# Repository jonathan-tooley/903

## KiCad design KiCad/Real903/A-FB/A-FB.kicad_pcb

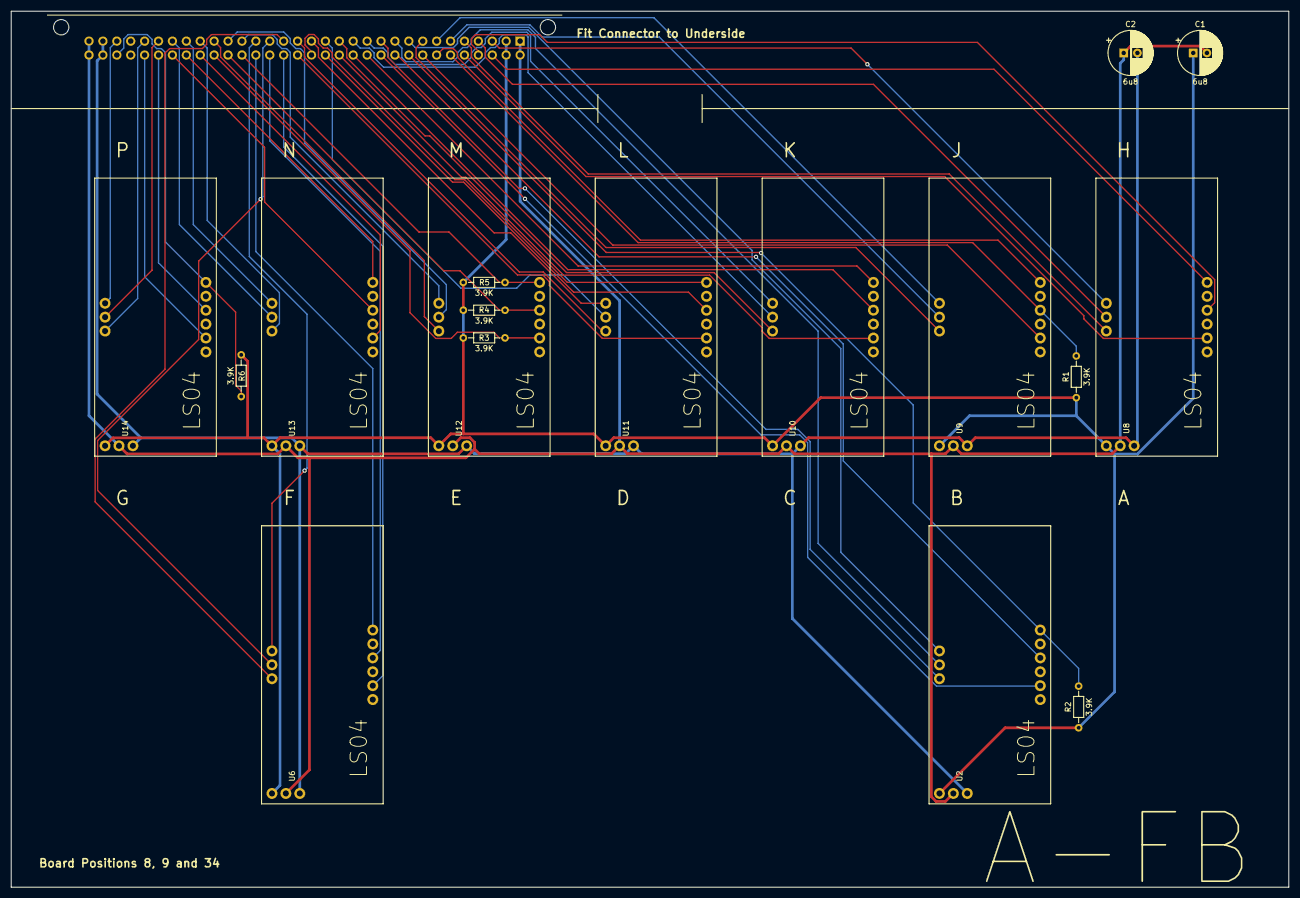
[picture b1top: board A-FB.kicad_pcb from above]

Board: 2 copper layers, 233.3 x 160.0 mm, 18 parts (1 on the bottom side), 57 nets.

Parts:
C1, C2: 6u8; CP_Radial_D8.0mm_P2.50mm
J1: J1; DIN41612_B_2x32_Horizontal
R1, R2, R3, R4, R5, R6: 3.9K; R_Axial_DIN0204_L3.6mm_D1.6mm_P7.62mm_Horizontal
U2, U6, U8, U9, U10, U11, U12, U13, U14: LS04; LSA

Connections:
3: J1.3, U8.13
4: J1.4, U8.12
5: J1.5, U8.11
6: J1.6, U9.12
6v: C1.1, J1.2, J1.B, R1.1, R2.1, R3.1, R4.1, R5.1, R6.1, U2.21, U6.21, U8.21, U9.21, U10.21, U11.21, U12.21, U13.21, U14.21
7: J1.7, U9.13
8: J1.8, U9.11
9: J1.9, U2.13
10: J1.10, U2.12
11: J1.11, U2.11
12: J1.12, U10.13
13: J1.13, U10.12
14: J1.14, U10.11
15: J1.15, U11.12
16: J1.16, U11.13
17: J1.17, U11.11
18: J1.18, U6.11
19: J1.19, U6.12
20: J1.20, U6.13
21: J1.21, U12.13
22: J1.22, U12.12
23: J1.23, U12.11
24: J1.24, U13.11
25: J1.25, U13.13
26: J1.26, U13.12
27: J1.27, U14.12
28: J1.28, U14.11
30: J1.30, U14.13
AA: J1.AA, R3.2, U12.2
AB: J1.AB, U13.2
AC: J1.AC, U13.6
AD: J1.AD, U13.4
AE: J1.AE, U14.4
AF: J1.AF, U14.2
AJ: J1.AJ, R6.2, U14.6
C: J1.C, U8.6
D: J1.D, U8.4
E: J1.E, U8.2
F: J1.F, R1.2, U9.4
GND: C1.2, C2.1, J1.1, J1.32, J1.A, J1.AL, U2.22, U6.22, U8.22, U9.22, U10.22, U11.22, U12.22, U13.22, U14.22
H: J1.H, U9.6
J: J1.J, U9.2
K: J1.K, R2.2, U2.6
L: J1.L, U2.4
M: J1.M, U2.2
N: J1.N, U10.6
Neg6v: C2.2, J1.31, J1.AK, U2.23, U6.23, U8.23, U9.23, U10.23, U11.23, U12.23, U13.23, U14.23
P: J1.P, U10.4
R: J1.R, U10.2
S: J1.S, U11.4
T: J1.T, U11.6
U: J1.U, U11.2
V: J1.V, U6.2
W: J1.W, U6.4
X: J1.X, U6.6
Y: J1.Y, R5.2, U12.6
Z: J1.Z, R4.2, U12.4

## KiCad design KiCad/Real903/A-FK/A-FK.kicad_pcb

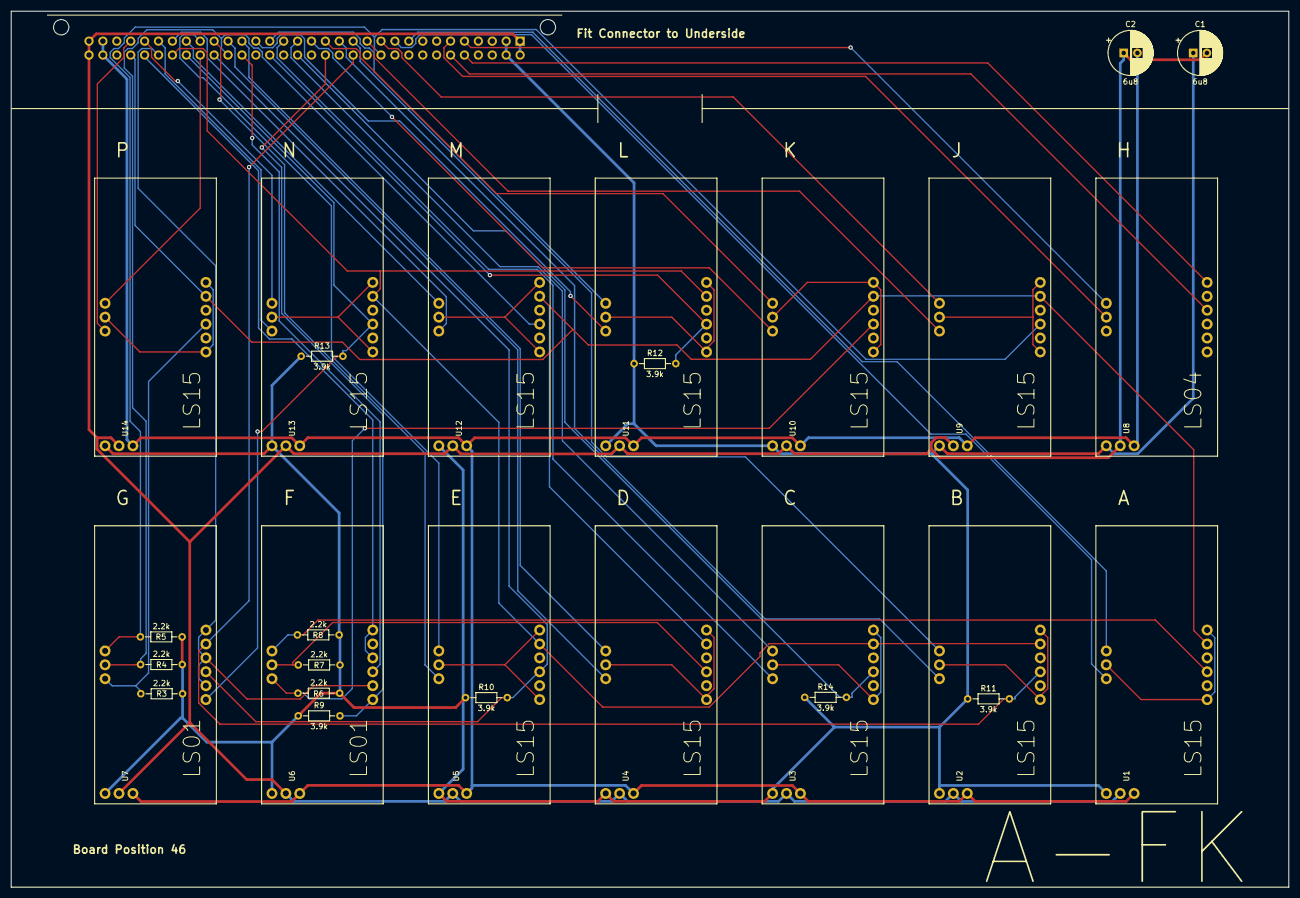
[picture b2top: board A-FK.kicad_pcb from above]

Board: 2 copper layers, 233.3 x 160.0 mm, 29 parts (1 on the bottom side), 57 nets.

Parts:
C1, C2: 6u8; CP_Radial_D8.0mm_P2.50mm
J1: J1; DIN41612_B_2x32_Horizontal
R3, R4, R5, R6, R7, R8: 2.2k; R_Axial_DIN0204_L3.6mm_D1.6mm_P7.62mm_Horizontal
R9, R10, R11, R12, R13, R14: 3.9k; R_Axial_DIN0204_L3.6mm_D1.6mm_P7.62mm_Horizontal
U1, U2, U3, U4, U5, U9, U10, U11, U12, U13, U14: LS15; LSA
U6, U7: LS01; LSA
U8: LS04; LSA

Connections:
6v: C1.1, J1.2, J1.B, R3.1, R4.1, R5.1, R6.1, R7.1, R8.1, R9.1, R10.1, R11.1, R12.1, R13.1, R14.1, U1.21, U2.21, U3.21, U4.21, U5.21, U6.21, U7.21, U8.21, U9.21, U10.21, U11.21, U12.21, U13.21, U14.21
CRS: J1.5, U8.13
CRSm: J1.E, U8.6
GND: C1.2, C2.1, J1.1, J1.32, J1.A, J1.AL, U1.22, U2.22, U3.22, U4.22, U5.22, U6.22, U7.22, U8.22, U9.22, U10.22, U11.22, U12.22, U13.22, U14.22
GTA1: J1.23, U5.11
GTA2: J1.24, U5.13
GTAa: J1.AA, R10.2, U5.3, U7.3
GTJ1: J1.13, U2.13
GTJ2: J1.14, U2.11
GTJa: J1.P, R11.2, U2.3, U7.5
GTM1: J1.19, U11.13
GTM2: J1.20, U11.11
GTMa: J1.W, R12.2, U11.3
GTQ1: J1.27, U13.11
GTQ2: J1.28, U13.13
GTQa: J1.AC, R13.2, U7.1, U13.3
MTPa: J1.Y, U6.3
Neg6v: C2.2, J1.31, J1.AK, U1.23, U2.23, U3.23, U4.23, U5.23, U6.23, U7.23, U8.23, U9.23, U10.23, U11.23, U12.23, U13.23, U14.23
unnamed: R3.2, U7.11, U14.3
unnamed: R6.2, U6.11, U10.3
unnamed: R7.2, U4.3, U6.12
unnamed: R8.2, U1.3, U6.13
unnamed: U1.1, U1.6, U1.12
unnamed: U2.1, U2.6, U2.12
unnamed: U3.1, U3.6, U3.12
unnamed: U4.1, U4.6, U4.12
unnamed: U5.1, U5.6, U5.12
unnamed: U9.1, U9.6, U9.12
unnamed: U10.1, U10.6, U10.12
unnamed: U11.1, U11.6, U11.12
unnamed: U12.1, U12.6, U12.12
unnamed: U13.1, U13.6, U13.12
unnamed: U14.1, U14.6, U14.12
OTA-1: J1.25, U12.13
OTA-2: J1.26, U12.11
OTA-': J1.Z, R4.2, U7.12, U12.3
OTG-1: J1.9, U1.13
OTG-2: J1.10, U1.11
OTJ-1: J1.11, U9.13
OTJ-2: J1.12, U9.11
OTJ-': J1.M, R5.2, U7.13, U9.3
OTM-1: J1.15, U10.13
OTM-2: J1.16, U10.11
OTMa: J1.S, R9.2, U6.1
OTP-1: J1.21, U4.13
OTP-2: J1.22, U4.11
OTQ-1: J1.29, U14.11
OTQ-2: J1.AB, U14.13
RESET-2: J1.AH, U1.5, U4.5, U9.5, U10.5, U12.5, U14.5
SFD: J1.6, U8.12
SFDm: J1.F, U8.4
WTM1: J1.17, U3.13
WTM2: J1.18, U3.11
WTMa: J1.U, R14.2, U3.3
t1: J1.AF, U6.4, U6.6
t3-2: J1.AE, U6.2, U7.2, U7.4, U7.6
t4: J1.AD, U2.5, U3.5, U5.5, U11.5, U13.5

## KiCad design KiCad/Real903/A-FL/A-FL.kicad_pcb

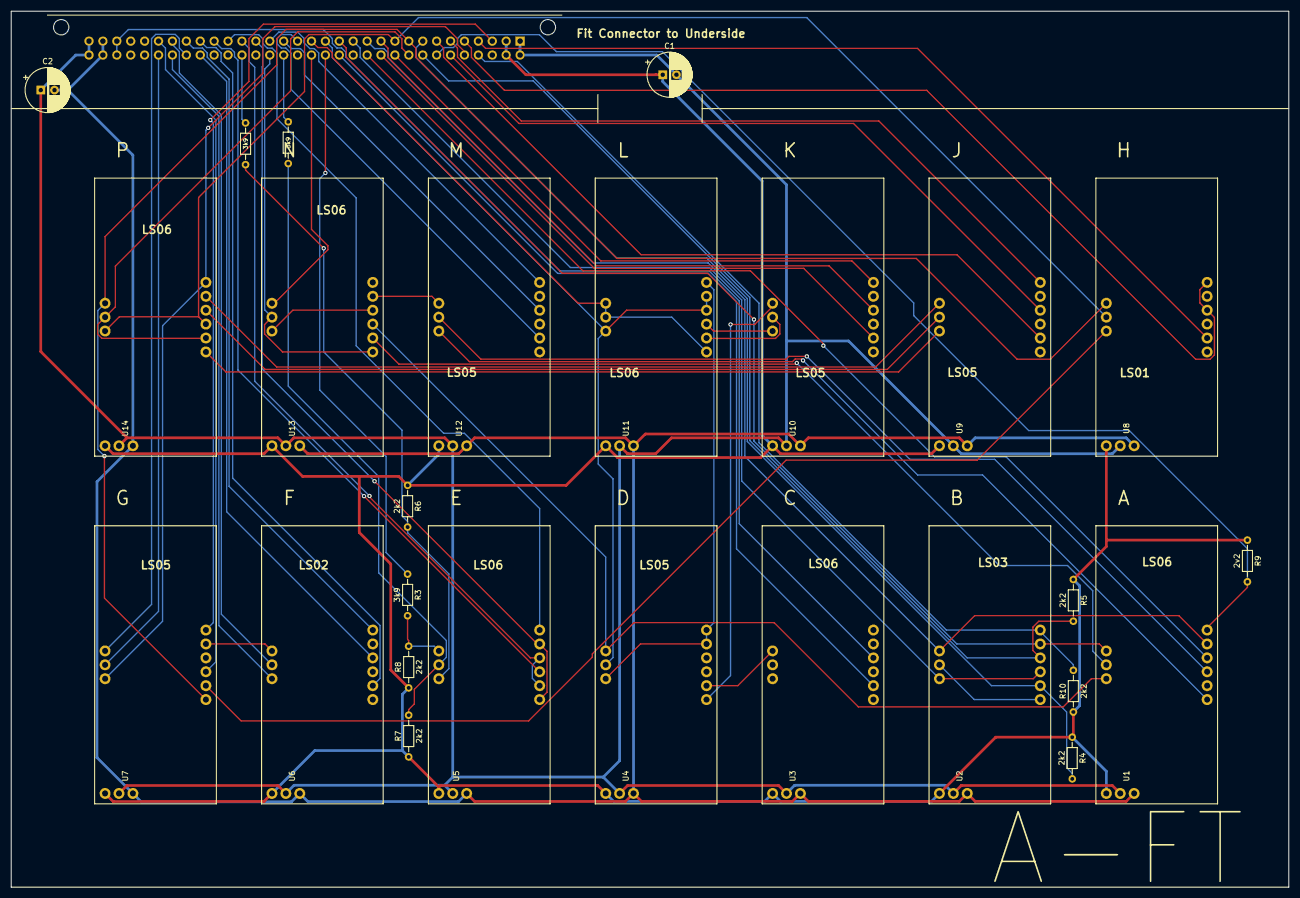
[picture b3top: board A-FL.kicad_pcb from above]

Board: 2 copper layers, 233.3 x 160.0 mm, 27 parts (1 on the bottom side), 68 nets.

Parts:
C1, C2: "6u8"; CP_Radial_D8.0mm_P2.50mm
J1: J1; DIN41612_B_2x32_Horizontal
R1, R2, R3: 3k9; R_Axial_DIN0204_L3.6mm_D1.6mm_P7.62mm_Horizontal
R4, R5, R6, R7, R8, R10: 2k2; R_Axial_DIN0204_L3.6mm_D1.6mm_P7.62mm_Horizontal
R9: 2v2; R_Axial_DIN0204_L3.6mm_D1.6mm_P7.62mm_Horizontal
U1, U2, U5, U7, U11, U13, U14: LS01; LSA
U3: LS14; LSA
U4: LS03; LSA
U6, U8, U9, U10, U12: LS18; LSA

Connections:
2.4v: J1.30, J1.AJ, U3.4
6v: C1.1, J1.2, J1.B, R4.1, R5.1, R6.1, R7.1, R8.1, R9.1, R10.1, U1.21, U2.21, U3.21, U4.21, U5.21, U6.21, U7.21, U8.21, U9.21, U10.21, U11.21, U12.21, U13.21, U14.21
AUTOk: J1.L, U10.6
CIN: J1.13, U2.3, U2.11
CINSk: J1.J, R5.2, U2.4
CS: J1.14, U1.13, U2.5
E1: J1.23, U5.3
E2: J1.22, U5.6
ENG: J1.9, U7.1, U8.13, U14.13
ENGk: J1.6, U9.6
GND: C1.2, C2.1, J1.1, J1.32, J1.A, J1.AL, U1.22, U2.22, U3.22, U4.22, U5.22, U6.22, U7.22, U8.22, U9.22, U10.22, U11.22, U12.22, U13.22, U14.22
JUMP: J1.16, U11.1, U11.12, U11.13
JUMPk: J1.M, U10.2
NG17k: J1.18, U12.4
Neg6v: C2.2, J1.31, J1.AK, U1.23, U2.23, U3.23, U4.23, U5.23, U6.23, U7.23, U8.23, U9.23, U10.23, U11.23, U12.23, U13.23, U14.23
unnamed: R1.2, R6.2, U5.11
unnamed: R2.2, R7.2, U5.12
unnamed: R3.2, R8.2, U5.13
unnamed: U1.1, U12.11
unnamed: U1.3, U12.12
unnamed: U1.11, U4.13, U13.3
unnamed: U1.12, U13.2
unnamed: U2.1, U2.12
unnamed: U3.13, U4.2
unnamed: U6.13, U7.5
unnamed: U7.2, U8.11
unnamed: U10.11, U11.3
unnamed: U10.12, U11.2
unnamed: U4.1, U10.13
unnamed: U4.5, U4.6, U4.11, U11.6
unnamed: U12.13, U13.5
unnamed: U13.4, U13.11
unnamed: U9.11, U14.1
unnamed: U9.12, U14.4
unnamed: U9.13, U14.5
ONG: J1.10, U8.12, U14.3, U14.11
ONGk: J1.7, U9.2
RESET: J1.AE, U7.12
RESETk: J1.24, U6.2
TCS: J1.26, U6.12
W17: J1.W, U13.1, U13.12
{ACTIVE1}: J1.Y, R1.1
{ACTIVE2}: J1.V, R2.1
{ACTIVE3}: J1.S, R3.1
~CINSk~: J1.8, R4.2, U2.2
~CSk~: J1.H, R9.2, U1.6
~CS~: J1.12, U1.5, U2.13
~E1~: J1.20, U5.1, U5.5
~E2~: J1.21, U5.2, U5.4
~ENGk~: J1.4, U8.2
~ENG~: J1.E, U7.11, U14.6
~JIA~: J1.R, U3.2
~JUMP~: J1.15, U4.12, U11.4, U11.5, U11.11
~JUMP~k: J1.11, U10.4
~NG17~k: J1.17, U12.2
~ONGk~: J1.F, U9.4
~ONG~: J1.K, U14.2, U14.12
~OS~: J1.T, U13.13
~OS~k: J1.19, U12.6
~RESET~: J1.AD, U6.11
~RESET~1: J1.27, U7.3
~RESTART~K: J1.3, U7.6
~SMNk~: J1.D, R10.2, U2.6
~STOP~: J1.AC, U7.13
~STOP~k: J1.25, U6.6
~TCS~k: J1.AB, U6.4
~TEST~k: J1.5, U8.4, U8.6
~WTM~a: J1.N, U1.4

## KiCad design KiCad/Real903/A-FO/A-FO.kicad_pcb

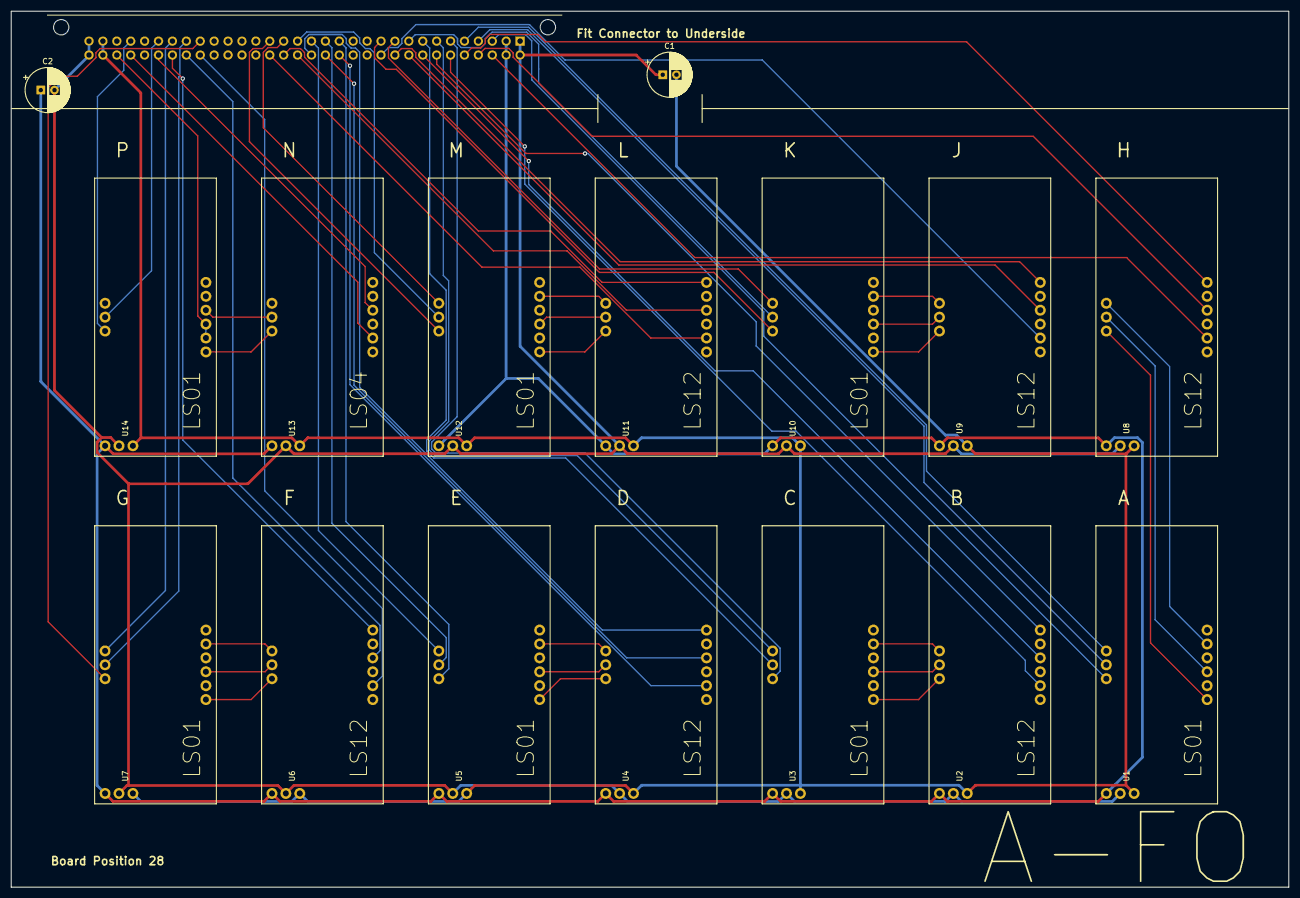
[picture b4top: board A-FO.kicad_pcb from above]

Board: 2 copper layers, 233.3 x 160.0 mm, 17 parts (1 on the bottom side), 64 nets.

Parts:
C1, C2: 6u8; CP_Radial_D8.0mm_P2.50mm
J1: J1; DIN41612_B_2x32_Horizontal
U1, U3, U5, U7, U10, U12, U14: LS01; LSA
U2, U4, U6, U8, U9, U11: LS12; LSA
U13: LS04; LSA

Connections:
6v: C2.1, J1.2, J1.B, U1.21, U2.21, U3.21, U4.21, U5.21, U6.21, U7.21, U8.21, U9.21, U10.21, U11.21, U12.21, U13.21, U14.21
GND: C1.1, C2.2, J1.1, J1.32, J1.A, J1.AL, U1.22, U2.22, U3.22, U4.22, U5.22, U6.22, U7.22, U8.22, U9.22, U10.22, U11.22, U12.22, U13.22, U14.22
IG1: J1.C, U8.2
IG2: J1.D, U8.4
IG3: J1.E, U8.6
IG4: J1.F, U2.2
IG5: J1.H, U2.6
IG6: J1.J, U2.4
IG7: J1.K, U9.4
IG8: J1.L, U9.6
IG9: J1.M, U9.2
IG10: J1.R, U4.2
IG11: J1.S, U4.4
IG12: J1.T, U4.6
IG13: J1.U, U11.4
IG14: J1.V, U11.6
IG15: J1.W, U11.2
IG16: J1.AB, U6.2
IG17: J1.AC, U6.4
IG18: J1.AD, U6.6
IP1: J1.3, U1.11
IP2: J1.4, U1.12
IP3: J1.5, U1.13
IP4: J1.6, U3.11
IP5: J1.7, U3.13
IP6: J1.8, U3.12
IP7: J1.9, U10.12
IP8: J1.10, U10.13
IP9: J1.11, U10.11
IP10: J1.14, U5.11
IP11: J1.15, U5.12
IP12: J1.16, U5.13
IP13: J1.17, U12.12
IP14: J1.18, U12.13
IP15: J1.19, U12.11
IP16: J1.24, U7.11
IP17: J1.25, U7.12
IP18: J1.26, U7.13
Neg6v: C1.2, J1.31, J1.AK, U1.23, U2.23, U3.23, U4.23, U5.23, U6.23, U7.23, U8.23, U9.23, U10.23, U11.23, U12.23, U13.23, U14.23
unnamed: U1.1, U8.11
unnamed: U1.3, U8.12
unnamed: U1.5, U8.13
unnamed: U2.11, U3.1
unnamed: U2.12, U3.3
unnamed: U2.13, U3.5
unnamed: U4.11, U5.1
unnamed: U4.12, U5.3
unnamed: U4.13, U5.5
unnamed: U6.11, U7.1
unnamed: U6.12, U7.3
unnamed: U6.13, U7.5
unnamed: U9.11, U10.1
unnamed: U9.12, U10.3
unnamed: U9.13, U10.5
unnamed: U11.11, U12.1
unnamed: U11.12, U12.3
unnamed: U11.13, U12.5
unnamed: U13.11, U14.1
unnamed: U13.12, U14.4
RBT: J1.27, U14.12
RBTm: J1.AE, U13.4
SBT: J1.29, U14.11
SBTm: J1.AH, U13.2
t4-2: J1.AJ, U14.2, U14.3

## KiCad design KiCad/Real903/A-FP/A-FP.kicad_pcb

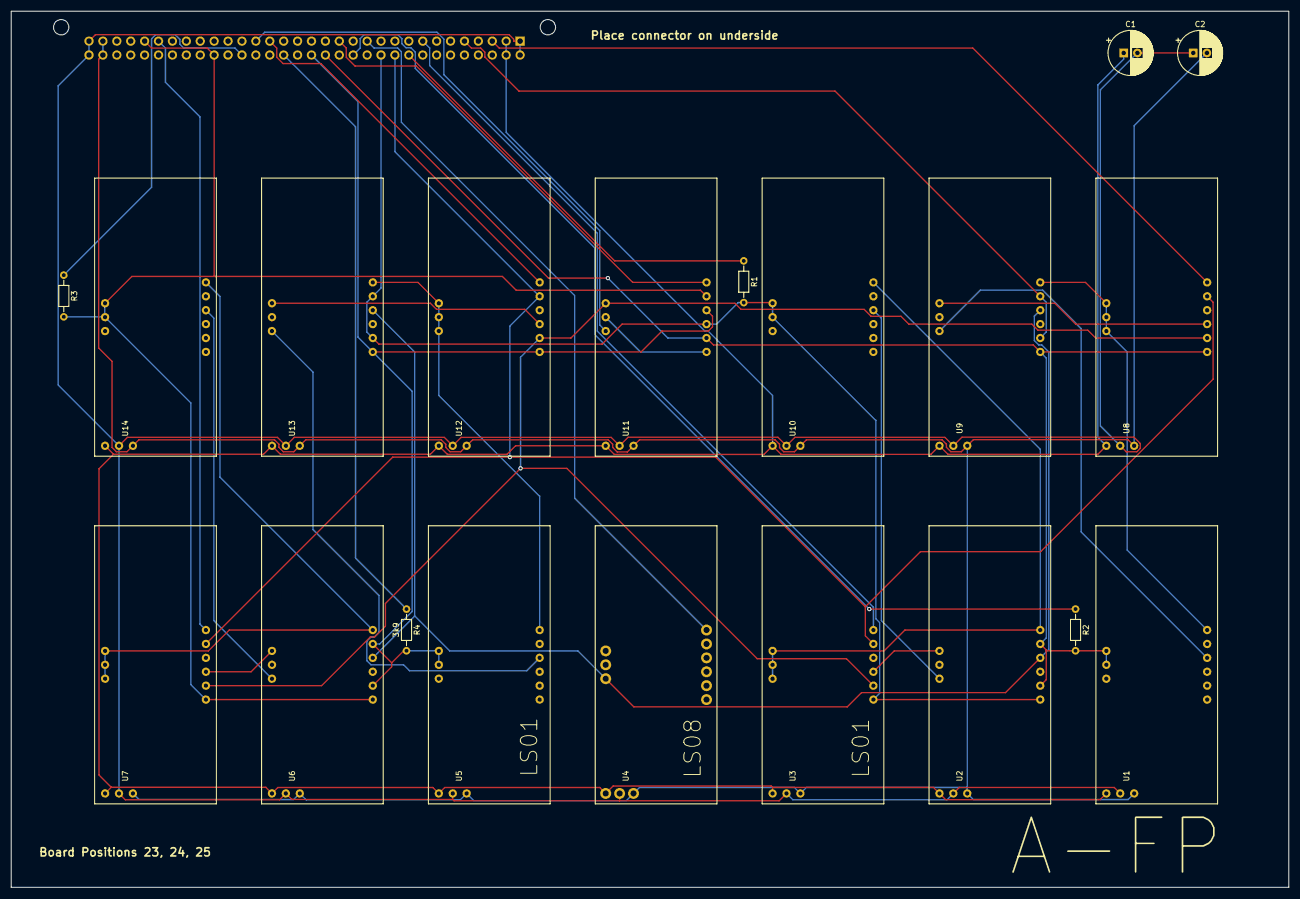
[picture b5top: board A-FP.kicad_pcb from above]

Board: 2 copper layers, 233.3 x 160.0 mm, 21 parts (1 on the bottom side), 35 nets.

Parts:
C1, C2: 6u8; CP_Radial_D8.0mm_P2.50mm
J1: J1; DIN41612_B_2x32_Horizontal
R1, R2, R3, R4: 3k9; R_Axial_DIN0204_L3.6mm_D1.6mm_P7.62mm_Horizontal
U1, U3, U5, U7, U8, U10, U12, U14: LS01; LSA
U2, U6, U9, U13: LS07; LSA
U4: LS08; LSA
U11: LS03; LSA

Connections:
1TPC-: J1.5, U9.2, U9.5
2.4vRef: U2.4, U4.11, U6.4, U9.4, U13.4
6v: C1.1, J1.2, J1.B, U1.21, U2.21, U3.21, U4.21, U5.21, U6.21, U7.21, U8.21, U9.21, U10.21, U11.21, U12.21, U13.21, U14.21
GND: C1.2, C2.1, J1.1, J1.32, J1.A, J1.AL, U1.22, U2.22, U3.22, U4.22, U5.22, U6.22, U7.22, U8.22, U9.22, U10.22, U11.22, U12.22, U13.22, U14.22
J1-: J1.3, U8.6
J2-: J1.8, U3.6
J3-: J1.19, U12.6
J4-: J1.27, U7.6
JTPC: J1.L, U3.5, U7.5, U8.5, U12.5
Neg6v: C2.2, J1.31, J1.AK, U1.23, U2.23, U3.23, U4.23, U5.23, U6.23, U7.23, U8.23, U9.23, U10.23, U11.23, U12.23, U13.23, U14.23
unnamed: U1.4, U9.11
unnamed: U1.6, U8.11, U8.12, U8.13, U9.6
unnamed: U2.13, U3.3
unnamed: U6.13, U7.3
unnamed: U8.3, U9.13
unnamed: U2.11, U10.4
unnamed: U2.6, U3.11, U3.12, U3.13, U10.6
unnamed: U11.1, U11.12
unnamed: U12.3, U13.13
unnamed: U5.6, U12.11, U12.12, U12.13, U13.6
unnamed: U5.4, U13.11
unnamed: U6.11, U14.4
unnamed: U6.6, U7.11, U7.12, U7.13, U14.6
PC1-: J1.S, R2.2, U1.12, U1.13, U2.2, U2.5, U8.1, U9.1, U11.2
PC1-4: J1.20, U11.11
PC2-: J1.M, R1.2, U2.1, U3.1, U10.12, U10.13, U11.3, U13.2, U13.5
PC3-: J1.T, R4.2, U5.12, U5.13, U6.2, U6.5, U11.4, U12.1, U13.1
PC4-: J1.28, J1.AA, R3.2, U6.1, U7.1, U11.5, U14.12, U14.13
PulseGenMargin: J1.12, U4.6
WFM-: U3.2, U7.2, U8.2, U11.13, U12.2
WFR: J1.14, U11.6
{PC1}: J1.P, R2.1
{PC2}: J1.K, R1.1
{PC3}: J1.V, R4.1
{PC4}: J1.Y, R3.1

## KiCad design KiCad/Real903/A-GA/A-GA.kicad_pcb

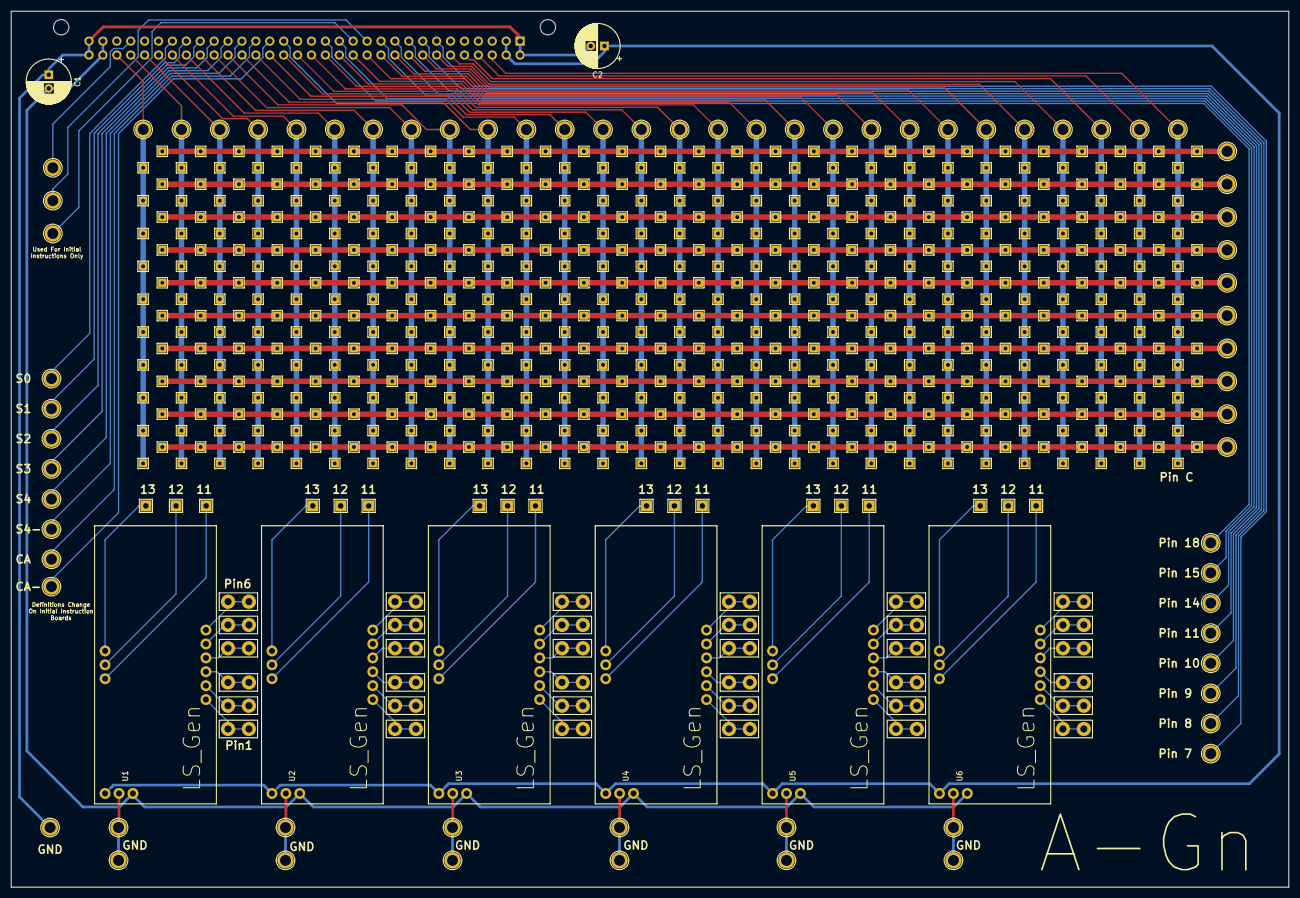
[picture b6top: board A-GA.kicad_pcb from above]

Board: 2 copper layers, 233.3 x 160.0 mm, 693 parts (1 on the bottom side), 120 nets.

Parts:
C1, C2: 6u8; CP_Radial_D8.0mm_P2.50mm
J1: J1; DIN41612_B_2x32_Horizontal
MH1, MH2, MH3, MH4, MH5, MH6, MH7, MH8, MH9, MH10, MH11, MH12, MH13, MH14, MH15, MH16, MH17, MH18, MH19, MH20, MH21, MH22, MH23, MH24, MH25, MH26, MH27, MH28, MH29, MH30, MH31, MH32, MH33, MH34, MH35, MH36, MH37, MH38, MH39, MH40, MH41, MH42, MH43, MH44, MH45, MH46, MH47, MH48, MH49, MH50, MH51, MH52, MH53, MH54, MH55, MH56, MH57, MH58, MH59, MH60, MH61, MH62, MH63, MH64, MH65, MH66, MH67, MH68, MH69, MH70, MH71, MH72, MH73, MH74, MH75, MH76, MH77, MH78, MH79, MH80, MH81, MH82, MH83, MH84, MH85, MH86, MH87, MH88, MH89, MH90, MH91, MH92, MH93, MH94, MH95, MH96, MH97, MH98, MH99, MH100, MH101, MH102, MH103, MH104, MH105, MH106, MH107, MH108, MH109, MH110, MH111, MH112, MH113, MH114, MH115, MH116, MH117, MH118, MH119, MH120, MH121, MH122, MH123, MH124, MH125, MH126, MH127, MH128, MH129, MH130, MH131, MH132, MH133, MH134, MH135, MH136, MH137, MH138, MH139, MH140, MH141, MH142, MH143, MH144, MH145, MH146, MH147, MH148, MH149, MH150, MH151, MH152, MH153, MH154, MH155, MH156, MH157, MH158, MH159, MH160, MH161, MH162, MH163, MH164, MH165, MH166, MH167, MH168, MH169, MH170, MH171, MH172, MH173, MH174, MH175, MH176, MH177, MH178, MH179, MH180, MH181, MH182, MH183, MH184, MH185, MH186, MH187, MH188, MH189, MH190, MH191, MH192, MH193, MH194, MH195, MH196, MH197, MH198, MH199, MH200, MH201, MH202, MH203, MH204, MH205, MH206, MH207, MH208, MH209, MH210, MH211, MH212, MH213, MH214, MH215, MH216, MH217, MH218, MH219, MH220, MH221, MH222, MH223, MH224, MH225, MH226, MH227, MH228, MH229, MH230, MH231, MH232, MH233, MH234, MH235, MH236, MH237, MH238, MH239, MH240, MH241, MH242, MH243, MH244, MH245, MH246, MH247, MH248, MH249, MH250, MH251, MH252, MH253, MH254, MH255, MH256, MH257, MH258, MH259, MH260, MH261, MH262, MH263, MH264, MH265, MH266, MH267, MH268, MH269, MH270, MH271, MH272, MH273, MH274, MH275, MH276, MH277, MH278, MH279, MH280, MH281, MH282, MH283, MH284, MH285, MH286, MH287, MH288, MH289, MH290, MH291, MH292, MH293, MH294, MH295, MH296, MH297, MH298, MH299, MH300, MH301, MH302, MH303, MH304, MH305, MH306, MH307, MH308, MH309, MH310, MH311, MH312, MH313, MH314, MH315, MH316, MH317, MH318, MH319, MH320, MH321, MH322, MH323, MH324, MH325, MH326, MH327, MH328, MH329, MH330, MH331, MH332, MH333, MH334, MH335, MH336, MH337, MH338, MH339, MH340, MH341, MH342, MH343, MH344, MH345, MH346, MH347, MH348, MH349, MH350, MH351, MH352, MH353, MH354, MH355, MH356, MH357, MH358, MH359, MH360, MH361, MH362, MH363, MH364, MH365, MH366, MH367, MH368, MH369, MH370, MH371, MH372, MH373, MH374, MH375, MH376, MH377, MH378, MH379, MH380, MH381, MH382, MH383, MH384, MH385, MH386, MH387, MH388, MH389, MH390, MH391, MH392, MH393, MH394, MH395, MH396, MH397, MH398, MH399, MH400, MH401, MH402, MH403, MH404, MH405, MH406, MH407, MH408, MH409, MH410, MH411, MH412, MH413, MH414, MH415, MH416, MH417, MH418, MH419, MH420, MH421, MH422, MH423, MH424, MH425, MH426, MH427, MH428, MH429, MH430, MH431, MH432, MH433, MH434, MH435, MH436, MH437, MH438, MH439, MH440, MH441, MH442, MH443, MH444, MH445, MH446, MH447, MH448, MH449, MH450, MH451, MH452, MH453, MH454, MH455, MH456, MH457, MH458, MH459, MH460, MH461, MH462, MH463, MH464, MH465, MH466, MH467, MH468, MH469, MH470, MH471, MH472, MH473, MH474, MH475, MH476, MH477, MH478, MH479, MH480, MH481, MH482, MH483, MH484, MH485, MH486, MH487, MH488, MH489, MH490, MH491, MH492, MH493, MH494, MH495, MH496, MH497, MH498, MH499, MH500, MH501, MH502, MH503, MH504, MH505, MH506, MH507, MH508, MH509, MH510, MH511, MH512, MH513, MH514, MH515, MH516, MH517, MH518, MH519, MH520, MH521, MH522, MH523, MH524, MH525, MH526, MH527, MH528, MH529, MH530, MH531, MH532, MH533, MH534, MH535, MH536, MH537, MH538, MH539, MH540, MH541, MH542, MH543, MH544, MH545, MH546, MH547, MH548, MH549, MH550, MH551, MH552, MH553, MH554, MH555, MH556, MH557, MH558, MH559, MH560: TestPoint_THTPad_1.5x1.5mm_Drill0.7mm
TPG0, TPG11, TPG12, TPG21, TPG22, TPG31, TPG32, TPG41, TPG42, TPG51, TPG52, TPG61, TPG62: TestPoint_Plated_Hole_D2.0mm
TPI7, TPI8, TPI9, TPI10, TPI11, TPI12, TPI13, TPI14, TPI15, TPI18, TPI19, TPI20, TPI21, TPI22, TPI23, TPI24, TPI25, TPI26, TPI29: TestPoint_Plated_Hole_D2.0mm
TPLA1, TPLA2, TPLA3, TPLA4, TPLA5, TPLA6: TestPoint_Bridge_Pitch3.81mm_Drill1.3mm
TPLA11, TPLA12, TPLA13: TestPoint_THTPad_2.0x2.0mm_Drill1.0mm
TPLB1, TPLB2, TPLB3, TPLB4, TPLB5, TPLB6: TestPoint_Bridge_Pitch3.81mm_Drill1.3mm
TPLB11, TPLB12, TPLB13: TestPoint_THTPad_2.0x2.0mm_Drill1.0mm
TPLBD13: TestPoint_THTPad_2.0x2.0mm_Drill1.0mm
TPLC1, TPLC2, TPLC3, TPLC4, TPLC5, TPLC6: TestPoint_Bridge_Pitch3.81mm_Drill1.3mm
TPLC11, TPLC12, TPLC13: TestPoint_THTPad_2.0x2.0mm_Drill1.0mm
TPLD1, TPLD2, TPLD3, TPLD4, TPLD5, TPLD6: TestPoint_Bridge_Pitch3.81mm_Drill1.3mm
TPLD11, TPLD12: TestPoint_THTPad_2.0x2.0mm_Drill1.0mm
TPLE1, TPLE2, TPLE3, TPLE4, TPLE5, TPLE6: TestPoint_Bridge_Pitch3.81mm_Drill1.3mm
TPLE11, TPLE12, TPLE13: TestPoint_THTPad_2.0x2.0mm_Drill1.0mm
TPLF1, TPLF2, TPLF3, TPLF4, TPLF5, TPLF6: TestPoint_Bridge_Pitch3.81mm_Drill1.3mm
TPLF11, TPLF12, TPLF13: TestPoint_THTPad_2.0x2.0mm_Drill1.0mm
TPX1, TPX2, TPX3, TPX4, TPX5, TPX6, TPX7, TPX8, TPX9, TPX10, TPX11, TPX12, TPX13, TPX14, TPX15, TPX16, TPX17, TPX18, TPX19, TPX20, TPX21, TPX22, TPX23, TPX24, TPX25, TPX26, TPX27, TPX28: TestPoint_Plated_Hole_D2.0mm
TPY1, TPY2, TPY3, TPY4, TPY5, TPY6, TPY7, TPY8, TPY9, TPY10: TestPoint_Plated_Hole_D2.0mm
U1, U2, U3, U4, U5, U6: LS_Gen; LSA

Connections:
6v: C2.1, J1.2, J1.B, U1.21, U2.21, U3.21, U4.21, U5.21, U6.21
7: J1.7, TPI7.1
8: J1.8, TPI8.1
9: J1.9, TPI9.1
10: J1.10, TPI10.1
11: J1.11, TPI11.1
12: J1.12, TPI12.1
13: J1.13, TPI13.1
14: J1.14, TPI14.1
15: J1.15, TPI15.1
18: J1.18, TPI18.1
29: J1.29, TPI29.1
AA: J1.AA, MH22.1, MH48.1, MH227.1, MH245.1, MH263.1, MH281.1, MH299.1, MH317.1, MH335.1, MH353.1, TPX8.1
AB: J1.AB, MH23.1, MH49.1, MH228.1, MH246.1, MH264.1, MH282.1, MH300.1, MH318.1, MH336.1, MH354.1, TPX7.1
AC: J1.AC, MH24.1, MH50.1, MH229.1, MH247.1, MH265.1, MH283.1, MH301.1, MH319.1, MH337.1, MH355.1, TPX6.1
AD: J1.AD, MH25.1, MH51.1, MH230.1, MH248.1, MH266.1, MH284.1, MH302.1, MH320.1, MH338.1, MH356.1, TPX5.1
AE: J1.AE, MH26.1, MH52.1, MH231.1, MH249.1, MH267.1, MH285.1, MH303.1, MH321.1, MH339.1, MH357.1, TPX4.1
AF: J1.AF, MH27.1, MH53.1, MH232.1, MH250.1, MH268.1, MH286.1, MH304.1, MH322.1, MH340.1, MH358.1, TPX3.1
AH: J1.AH, MH28.1, MH54.1, MH233.1, MH251.1, MH269.1, MH287.1, MH305.1, MH323.1, MH341.1, MH359.1, TPX2.1
AJ: J1.AJ, MH29.1, MH55.1, MH234.1, MH252.1, MH270.1, MH288.1, MH306.1, MH324.1, MH342.1, MH360.1, TPX1.1
C: J1.C, MH361.1, MH381.1, MH401.1, MH421.1, MH441.1, MH461.1, MH481.1, MH501.1, MH521.1, MH541.1, TPX28.1
CA: J1.20, TPI20.1
CA-: J1.19, TPI19.1
D: J1.D, MH362.1, MH382.1, MH402.1, MH422.1, MH442.1, MH462.1, MH482.1, MH502.1, MH522.1, MH542.1, TPX27.1
E: J1.E, MH363.1, MH383.1, MH403.1, MH423.1, MH443.1, MH463.1, MH483.1, MH503.1, MH523.1, MH543.1, TPX26.1
F: J1.F, MH364.1, MH384.1, MH404.1, MH424.1, MH444.1, MH464.1, MH484.1, MH504.1, MH524.1, MH544.1, TPX25.1
GND: C1.1, C2.2, J1.1, J1.32, J1.A, J1.AL, TPG0.1
H: J1.H, MH365.1, MH385.1, MH405.1, MH425.1, MH445.1, MH465.1, MH485.1, MH505.1, MH525.1, MH545.1, TPX24.1
J: J1.J, MH366.1, MH386.1, MH406.1, MH426.1, MH446.1, MH466.1, MH486.1, MH506.1, MH526.1, MH546.1, TPX23.1
K: J1.K, MH367.1, MH387.1, MH407.1, MH427.1, MH447.1, MH467.1, MH487.1, MH507.1, MH527.1, MH547.1, TPX22.1
L: J1.L, MH368.1, MH388.1, MH408.1, MH428.1, MH448.1, MH468.1, MH488.1, MH508.1, MH528.1, MH548.1, TPX21.1
M: J1.M, MH369.1, MH389.1, MH409.1, MH429.1, MH449.1, MH469.1, MH489.1, MH509.1, MH529.1, MH549.1, TPX20.1
N: J1.N, MH370.1, MH390.1, MH410.1, MH430.1, MH450.1, MH470.1, MH490.1, MH510.1, MH530.1, MH550.1, TPX19.1
Neg6v: C1.2, J1.31, J1.AK, U1.23, U2.23, U3.23, U4.23, U5.23, U6.23
unnamed: MH2.1, MH3.1, MH4.1, MH5.1, MH6.1, MH7.1, MH8.1, MH9.1, MH10.1, MH30.1, MH31.1, MH32.1, MH33.1, MH34.1, MH35.1, MH36.1, MH37.1, MH38.1, MH371.1, MH372.1, MH373.1, MH374.1, MH375.1, MH376.1, MH377.1, MH378.1, MH379.1, MH380.1, TPY1.1
unnamed: MH12.1, MH56.1, MH57.1, MH58.1, MH59.1, MH60.1, MH61.1, MH62.1, MH63.1, MH64.1, MH65.1, MH66.1, MH67.1, MH68.1, MH69.1, MH70.1, MH71.1, MH72.1, MH391.1, MH392.1, MH393.1, MH394.1, MH395.1, MH396.1, MH397.1, MH398.1, MH399.1, MH400.1, TPY2.1
unnamed: MH92.1, MH93.1, MH94.1, MH95.1, MH96.1, MH97.1, MH98.1, MH99.1, MH100.1, MH101.1, MH102.1, MH103.1, MH104.1, MH105.1, MH106.1, MH107.1, MH108.1, MH109.1, MH431.1, MH432.1, MH433.1, MH434.1, MH435.1, MH436.1, MH437.1, MH438.1, MH439.1, MH440.1, TPY4.1
unnamed: MH110.1, MH111.1, MH112.1, MH113.1, MH114.1, MH115.1, MH116.1, MH117.1, MH118.1, MH119.1, MH120.1, MH121.1, MH122.1, MH123.1, MH124.1, MH125.1, MH126.1, MH127.1, MH451.1, MH452.1, MH453.1, MH454.1, MH455.1, MH456.1, MH457.1, MH458.1, MH459.1, MH460.1, TPY5.1
unnamed: MH128.1, MH129.1, MH130.1, MH131.1, MH132.1, MH133.1, MH134.1, MH135.1, MH136.1, MH137.1, MH138.1, MH139.1, MH140.1, MH141.1, MH142.1, MH143.1, MH144.1, MH145.1, MH471.1, MH472.1, MH473.1, MH474.1, MH475.1, MH476.1, MH477.1, MH478.1, MH479.1, MH480.1, TPY6.1
unnamed: MH146.1, MH147.1, MH148.1, MH149.1, MH150.1, MH151.1, MH152.1, MH153.1, MH154.1, MH155.1, MH156.1, MH157.1, MH158.1, MH159.1, MH160.1, MH161.1, MH162.1, MH163.1, MH491.1, MH492.1, MH493.1, MH494.1, MH495.1, MH496.1, MH497.1, MH498.1, MH499.1, MH500.1, TPY7.1
unnamed: MH164.1, MH165.1, MH166.1, MH167.1, MH168.1, MH169.1, MH170.1, MH171.1, MH172.1, MH173.1, MH174.1, MH175.1, MH176.1, MH177.1, MH178.1, MH179.1, MH180.1, MH181.1, MH511.1, MH512.1, MH513.1, MH514.1, MH515.1, MH516.1, MH517.1, MH518.1, MH519.1, MH520.1, TPY8.1
unnamed: MH182.1, MH183.1, MH184.1, MH185.1, MH186.1, MH187.1, MH188.1, MH189.1, MH190.1, MH191.1, MH192.1, MH193.1, MH194.1, MH195.1, MH196.1, MH197.1, MH198.1, MH199.1, MH531.1, MH532.1, MH533.1, MH534.1, MH535.1, MH536.1, MH537.1, MH538.1, MH539.1, MH540.1, TPY9.1
unnamed: MH200.1, MH201.1, MH202.1, MH203.1, MH204.1, MH205.1, MH206.1, MH207.1, MH208.1, MH209.1, MH210.1, MH211.1, MH212.1, MH213.1, MH214.1, MH215.1, MH216.1, MH217.1, MH551.1, MH552.1, MH553.1, MH554.1, MH555.1, MH556.1, MH557.1, MH558.1, MH559.1, MH560.1, TPY10.1
unnamed: MH74.1, MH75.1, MH76.1, MH77.1, MH78.1, MH79.1, MH80.1, MH81.1, MH82.1, MH83.1, MH84.1, MH85.1, MH86.1, MH87.1, MH88.1, MH89.1, MH90.1, MH91.1, MH411.1, MH412.1, MH413.1, MH414.1, MH415.1, MH416.1, MH417.1, MH418.1, MH419.1, MH420.1, TPY3.1
unnamed: TPG11.1, TPG12.1, U1.22
unnamed: TPG21.1, TPG22.1, U2.22
unnamed: TPG31.1, TPG32.1, U3.22
unnamed: TPG41.1, TPG42.1, U4.22
unnamed: TPG51.1, TPG52.1, U5.22
unnamed: TPG61.1, TPG62.1, U6.22
unnamed: TPLA1.1, U1.1
unnamed: TPLA2.1, U1.2
unnamed: TPLA3.1, U1.3
unnamed: TPLA4.1, U1.4
unnamed: TPLA5.1, U1.5
unnamed: TPLA6.1, U1.6
unnamed: TPLA11.1, U1.11
unnamed: TPLA12.1, U1.12
unnamed: TPLA13.1, U1.13
unnamed: TPLB1.1, U2.1
unnamed: TPLB2.1, U2.2
unnamed: TPLB3.1, U2.3
unnamed: TPLB4.1, U2.4
unnamed: TPLB5.1, U2.5
unnamed: TPLB6.1, U2.6
unnamed: TPLB11.1, U2.11
unnamed: TPLB12.1, U2.12
unnamed: TPLB13.1, U2.13
unnamed: TPLBD13.1, U4.13
unnamed: TPLC1.1, U3.1
unnamed: TPLC2.1, U3.2
unnamed: TPLC3.1, U3.3
unnamed: TPLC4.1, U3.4
unnamed: TPLC5.1, U3.5
unnamed: TPLC6.1, U3.6
unnamed: TPLC11.1, U3.11
unnamed: TPLC12.1, U3.12
unnamed: TPLC13.1, U3.13
unnamed: TPLD1.1, U4.1
unnamed: TPLD2.1, U4.2
unnamed: TPLD3.1, U4.3
unnamed: TPLD4.1, U4.4
unnamed: TPLD5.1, U4.5
unnamed: TPLD6.1, U4.6
unnamed: TPLD11.1, U4.11
unnamed: TPLD12.1, U4.12
unnamed: TPLE1.1, U5.1
unnamed: TPLE2.1, U5.2
unnamed: TPLE3.1, U5.3
unnamed: TPLE4.1, U5.4
unnamed: TPLE5.1, U5.5
unnamed: TPLE6.1, U5.6
unnamed: TPLE11.1, U5.11
unnamed: TPLE12.1, U5.12
unnamed: TPLE13.1, U5.13
unnamed: TPLF1.1, U6.1
unnamed: TPLF2.1, U6.2
unnamed: TPLF3.1, U6.3
unnamed: TPLF4.1, U6.4
unnamed: TPLF5.1, U6.5
unnamed: TPLF6.1, U6.6
unnamed: TPLF11.1, U6.11
unnamed: TPLF12.1, U6.12
unnamed: TPLF13.1, U6.13
P: J1.P, MH1.1, MH11.1, MH73.1, MH235.1, MH253.1, MH271.1, MH289.1, MH307.1, MH325.1, MH343.1, TPX18.1
R: J1.R, MH13.1, MH39.1, MH218.1, MH236.1, MH254.1, MH272.1, MH290.1, MH308.1, MH326.1, MH344.1, TPX17.1
S: J1.S, MH14.1, MH40.1, MH219.1, MH237.1, MH255.1, MH273.1, MH291.1, MH309.1, MH327.1, MH345.1, TPX16.1
S0: J1.26, TPI26.1
S1: J1.25, TPI25.1
S2: J1.24, TPI24.1
S3: J1.23, TPI23.1
S4: J1.22, TPI22.1
S4-: J1.21, TPI21.1
T: J1.T, MH15.1, MH41.1, MH220.1, MH238.1, MH256.1, MH274.1, MH292.1, MH310.1, MH328.1, MH346.1, TPX15.1
U: J1.U, MH16.1, MH42.1, MH221.1, MH239.1, MH257.1, MH275.1, MH293.1, MH311.1, MH329.1, MH347.1, TPX14.1
V: J1.V, MH17.1, MH43.1, MH222.1, MH240.1, MH258.1, MH276.1, MH294.1, MH312.1, MH330.1, MH348.1, TPX13.1
W: J1.W, MH18.1, MH44.1, MH223.1, MH241.1, MH259.1, MH277.1, MH295.1, MH313.1, MH331.1, MH349.1, TPX12.1
X: J1.X, MH19.1, MH45.1, MH224.1, MH242.1, MH260.1, MH278.1, MH296.1, MH314.1, MH332.1, MH350.1, TPX11.1
Y: J1.Y, MH20.1, MH46.1, MH225.1, MH243.1, MH261.1, MH279.1, MH297.1, MH315.1, MH333.1, MH351.1, TPX10.1
Z: J1.Z, MH21.1, MH47.1, MH226.1, MH244.1, MH262.1, MH280.1, MH298.1, MH316.1, MH334.1, MH352.1, TPX9.1
